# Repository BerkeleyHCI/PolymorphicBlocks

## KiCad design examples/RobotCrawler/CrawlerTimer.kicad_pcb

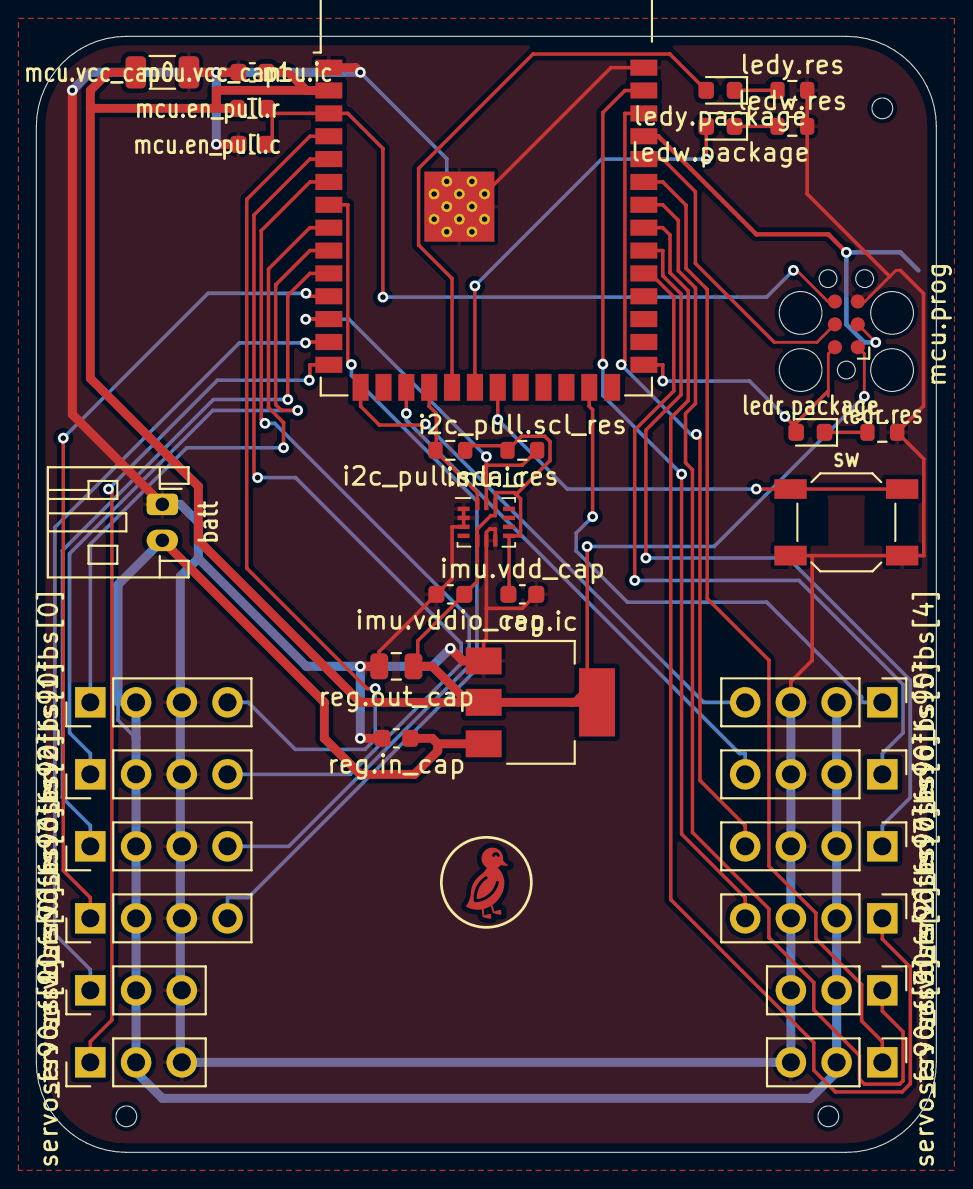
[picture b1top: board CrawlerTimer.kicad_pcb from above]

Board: 2 copper layers, 50.0 x 62.0 mm, 38 parts (0 on the bottom side), 35 nets.

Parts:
U4: Symbol_DucklingSolid
batt: S2B-PH-K; JST_PH_S2B-PH-K_1x02_P2.00mm_Horizontal
i2c_pull.scl_res, i2c_pull.sda_res: R_0603_1608Metric
imu.ic: LSM6DS3TR-C; Bosch_LGA-14_3x2.5mm_P0.5mm
imu.vdd_cap, imu.vddio_cap: C_0603_1608Metric
jlc_th.th1, jlc_th.th2, jlc_th.th3: JlcToolingHole_1.152mm
ledr.package: Red 615~630nm 1.9~2.2V 0603 Light Emitting Diodes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; LED_0603_1608Metric
ledr.res: R_0603_1608Metric
ledw.package: Red 615~630nm 1.9~2.2V 0603 Light Emitting Diodes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; LED_0603_1608Metric
ledw.res: R_0603_1608Metric
ledy.package: Red 615~630nm 1.9~2.2V 0603 Light Emitting Diodes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; LED_0603_1608Metric
ledy.res: R_0603_1608Metric
mcu.en_pull.c, mcu.vcc_cap1: C_0603_1608Metric
mcu.en_pull.r: R_0603_1608Metric
mcu.ic: ESP32-S3-WROOM-1-N16R8; ESP32-S3-WROOM-1
mcu.prog: Tag-Connect_TC2030-IDC-FP_2x03_P1.27mm_Vertical
mcu.vcc_cap0: C_1206_3216Metric
reg.ic: LDL1117S33R; SOT-223-3_TabPin2
reg.in_cap: C_0603_1608Metric
reg.out_cap: C_0805_2012Metric
servo_fs90fbs[0], servo_fs90fbs[1], servo_fs90fbs[2], servo_fs90fbs[3], servo_fs90fbs[4], servo_fs90fbs[5], servo_fs90fbs[6], servo_fs90fbs[7]: PinHeader2.54 1x4; PinHeader_1x04_P2.54mm_Vertical
servo_fs90rs[0], servo_fs90rs[1], servo_fs90rs[2], servo_fs90rs[3]: PinHeader2.54 1x3; PinHeader_1x03_P2.54mm_Vertical
sw: 5.1mm switch; SW_SPST_SKQG_WithoutStem

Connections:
batt.gnd: batt.1, imu.ic.1, imu.ic.2, imu.ic.3, imu.ic.6, imu.ic.7, imu.vdd_cap.2, imu.vddio_cap.2, ledr.res.2, ledw.res.2, ledy.res.2, mcu.en_pull.c.2, mcu.ic.1, mcu.ic.40, mcu.ic.41, mcu.prog.5, mcu.vcc_cap0.2, mcu.vcc_cap1.2, reg.ic.1, reg.in_cap.2, reg.out_cap.2, servo_fs90fbs[0].3, servo_fs90fbs[1].3, servo_fs90fbs[2].3, servo_fs90fbs[3].3, servo_fs90fbs[4].3, servo_fs90fbs[5].3, servo_fs90fbs[6].3, servo_fs90fbs[7].3, servo_fs90rs[0].3, servo_fs90rs[1].3, servo_fs90rs[2].3, servo_fs90rs[3].3, sw.2
batt.pwr: batt.2, reg.ic.3, reg.in_cap.1, servo_fs90fbs[0].2, servo_fs90fbs[1].2, servo_fs90fbs[2].2, servo_fs90fbs[3].2, servo_fs90fbs[4].2, servo_fs90fbs[5].2, servo_fs90fbs[6].2, servo_fs90fbs[7].2, servo_fs90rs[0].2, servo_fs90rs[1].2, servo_fs90rs[2].2, servo_fs90rs[3].2
i2c_pull.i2c.scl: i2c_pull.scl_res.2, imu.ic.13, mcu.ic.12
i2c_pull.i2c.sda: i2c_pull.sda_res.2, imu.ic.14, mcu.ic.18
imu.pwr: i2c_pull.scl_res.1, i2c_pull.sda_res.1, imu.ic.5, imu.ic.8, imu.ic.12, imu.vdd_cap.1, imu.vddio_cap.1, mcu.en_pull.r.1, mcu.ic.2, mcu.prog.1, mcu.vcc_cap0.1, mcu.vcc_cap1.1, reg.ic.2, reg.out_cap.1
ledr.res.a: ledr.package.1, ledr.res.1
ledw.res.a: ledw.package.1, ledw.res.1
ledw.signal: ledw.package.2, mcu.ic.20
ledy.res.a: ledy.package.1, ledy.res.1
ledy.signal: ledy.package.2, mcu.ic.19
mcu.program_boot_node: ledr.package.2, mcu.ic.27, mcu.prog.2
mcu.program_en_node: mcu.en_pull.c.1, mcu.en_pull.r.2, mcu.ic.3, mcu.prog.6
mcu.program_uart_node.a_tx: mcu.ic.37, mcu.prog.3
mcu.program_uart_node.b_tx: mcu.ic.36, mcu.prog.4
servo_fs90fbs[0].fb: mcu.ic.4, servo_fs90fbs[0].4
servo_fs90fbs[0].pwm: mcu.ic.8, servo_fs90fbs[0].1
servo_fs90fbs[1].fb: mcu.ic.5, servo_fs90fbs[1].4
servo_fs90fbs[1].pwm: mcu.ic.9, servo_fs90fbs[1].1
servo_fs90fbs[2].fb: mcu.ic.6, servo_fs90fbs[2].4
servo_fs90fbs[2].pwm: mcu.ic.10, servo_fs90fbs[2].1
servo_fs90fbs[3].fb: mcu.ic.7, servo_fs90fbs[3].4
servo_fs90fbs[3].pwm: mcu.ic.11, servo_fs90fbs[3].1
servo_fs90fbs[4].fb: mcu.ic.15, servo_fs90fbs[4].4
servo_fs90fbs[4].pwm: mcu.ic.25, servo_fs90fbs[4].1
servo_fs90fbs[5].fb: mcu.ic.17, servo_fs90fbs[5].4
servo_fs90fbs[5].pwm: mcu.ic.31, servo_fs90fbs[5].1
servo_fs90fbs[6].fb: mcu.ic.38, servo_fs90fbs[6].4
servo_fs90fbs[6].pwm: mcu.ic.32, servo_fs90fbs[6].1
servo_fs90fbs[7].fb: mcu.ic.39, servo_fs90fbs[7].4
servo_fs90fbs[7].pwm: mcu.ic.33, servo_fs90fbs[7].1
servo_fs90rs[0].pwm: mcu.ic.13, servo_fs90rs[0].1
servo_fs90rs[1].pwm: mcu.ic.14, servo_fs90rs[1].1
servo_fs90rs[2].pwm: mcu.ic.34, servo_fs90rs[2].1
servo_fs90rs[3].pwm: mcu.ic.35, servo_fs90rs[3].1
sw.out: mcu.ic.21, sw.1

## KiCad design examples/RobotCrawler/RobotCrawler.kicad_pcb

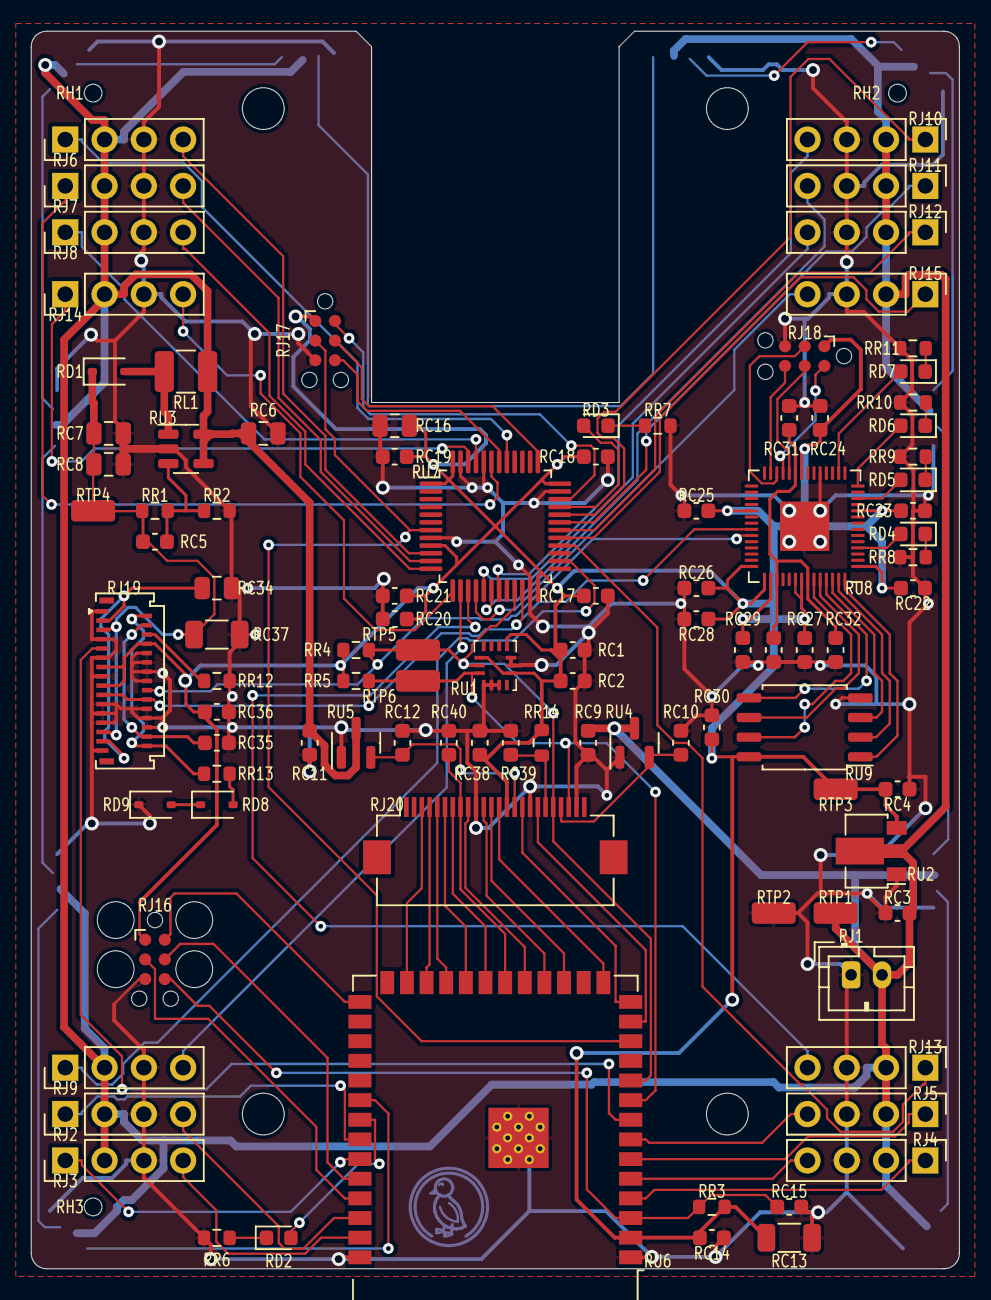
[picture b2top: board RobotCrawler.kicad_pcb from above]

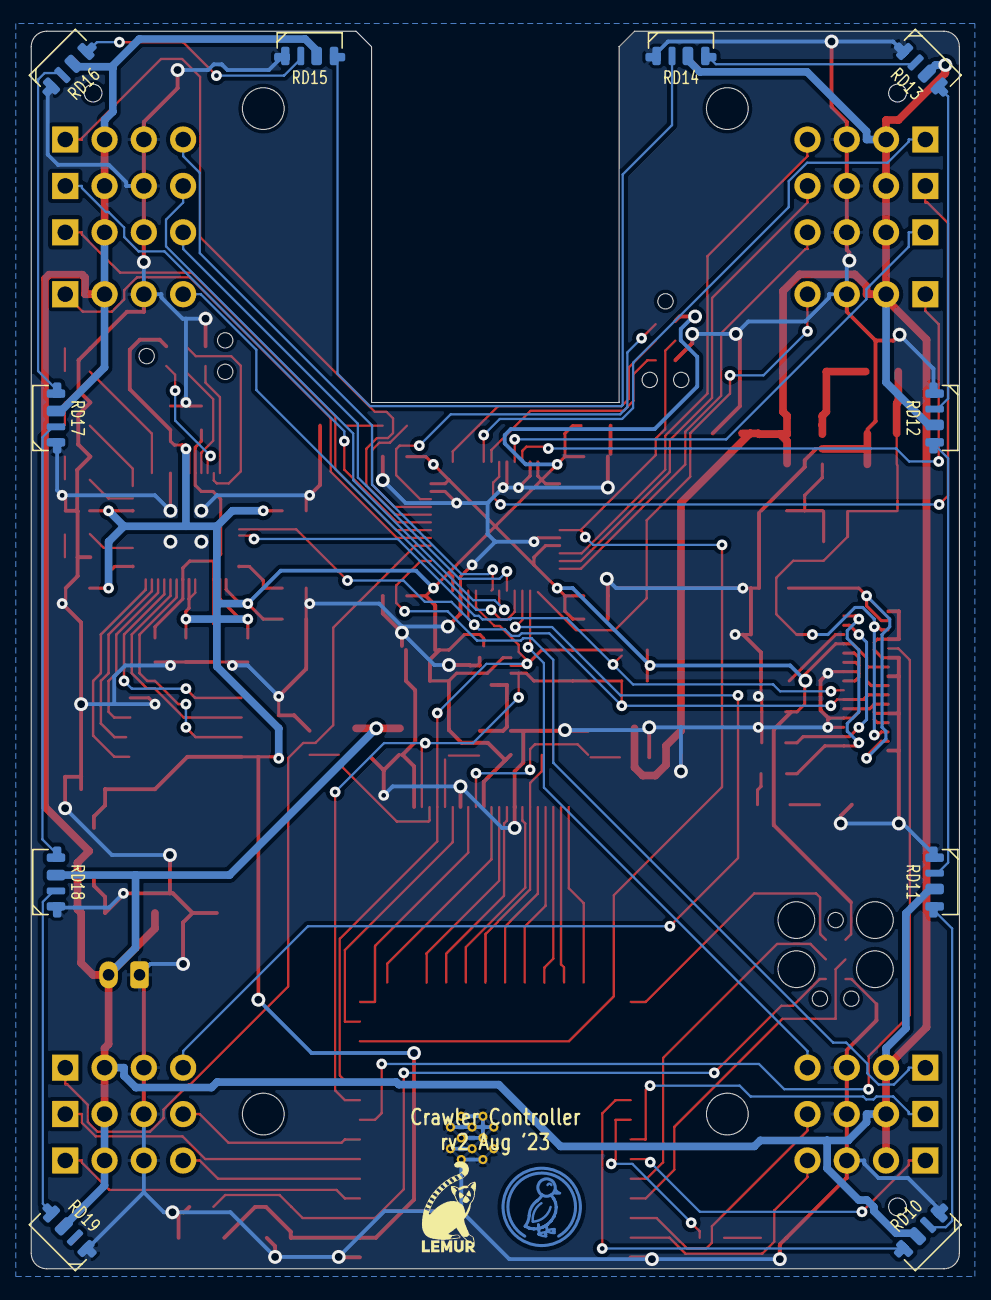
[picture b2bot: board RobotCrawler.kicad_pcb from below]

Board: 2 copper layers, 60.0 x 80.0 mm, 118 parts (12 on the bottom side), 99 nets.

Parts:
H10, H11, H12, H14: MountingHole_2.7mm_M2.5
RC1, RC2, RC3, RC4, RC5, RC9, RC10, RC11, RC12, RC14, RC15, RC17, RC18, RC19, RC20, RC21, RC22, RC23, RC24, RC25, RC26, RC27, RC28, RC29, RC30, RC31, RC32, RC33, RC35, RC36, RC38, RC39, RC40: C_0603_1608Metric
RC6, RC7, RC8, RC16, RC34: C_0805_2012Metric
RC13, RC37: C_1206_3216Metric
RD1: CUS10S30,H3F (TOSHIBA) - 30V 230mV@100mA 1A SOD-3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; D_SOD-323
RD2, RD3, RD4, RD5, RD6, RD7: LED_0603_1608Metric
RD8, RD9: 1N5819WS (Guangdong Hottech) - 40V 600mV@1A 1A SO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; D_SOD-323
RD10, RD11, RD12, RD13, RD14, RD15, RD16, RD17, RD18, RD19: SK6812 SIDE-A (Normand Electronic Co Ltd); LED_SK6812-SIDE-A
RH1, RH2, RH3: JlcToolingHole_1.152mm
RJ1: B2B-PH-K (JST); JST_PH_B2B-PH-K_1x02_P2.00mm_Vertical
RJ2, RJ3, RJ4, RJ5, RJ6, RJ7, RJ8, RJ9, RJ10, RJ11, RJ12, RJ13, RJ14, RJ15: PinHeader2.54 1x4 (Generic); PinHeader_1x04_P2.54mm_Vertical
RJ16: Tag-Connect_TC2030-IDC-FP_2x03_P1.27mm_Vertical
RJ17, RJ18: Tag-Connect_TC2030-IDC-NL_2x03_P1.27mm_Vertical
RJ19: FH35C-31S-0.3SHW (Hirose); Hirose_FH35C-31S-0.3SHW_1x31-1MP_P0.30mm_Horizontal
RJ20: AFC01-S24FCA-00 (Jushuo); Hirose_FH12-24S-0.5SH_1x24-1MP_P0.50mm_Horizontal
RL1: L_1210_3225Metric
RR1, RR2, RR3, RR4, RR5, RR6, RR7, RR8, RR9, RR10, RR11, RR12, RR13, RR14: R_0603_1608Metric
RTP1: 5015 (Keystone) - vbatt; TestPoint_TE_RCT_0805
RTP2: 5015 (Keystone) - gnd; TestPoint_TE_RCT_0805
RTP3: 5015 (Keystone) - v3v3; TestPoint_TE_RCT_0805
RTP4: 5015 (Keystone) - v14; TestPoint_TE_RCT_0805
RTP5: 5015 (Keystone) - i2c_chain_0.scl; TestPoint_TE_RCT_0805
RTP6: 5015 (Keystone) - i2c_tp._io_sda_link; TestPoint_TE_RCT_0805
RU1: LSM6DS3TR-C (STMicroelectronics); Bosch_LGA-14_3x2.5mm_P0.5mm
RU2: AP7215-33YG-13 (Diodes Incorporated); SOT-89-3
RU3: TPS61040DBVR (Texas Instruments); SOT-23-5
RU4: XC6206P252MR (Torex Semiconductor Ltd); SOT-23
RU5: XC6206P122MR-G (Torex Semiconductor Ltd); SOT-23
RU6: ESP32-S3-WROOM-1-N16R8 (Espressif Systems); ESP32-S3-WROOM-1
RU7: STM32F103xxT6 (STMicroelectronics); LQFP-48_7x7mm_P0.5mm
RU8: RP2040 (Raspberry Pi); QFN-56-1EP_7x7mm_P0.4mm_EP3.2x3.2mm
RU9: W25Q128JVSIQ (Winbond Electronics); SOIC-8_5.23x5.23mm_P1.27mm
UU4: Duck; Symbol_Duckling
UU5: Lemur; Symbol_LemurSmall

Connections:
Rcam.device.reset: RC39.1, RJ20.19, RR14.2
Rcam.dvp8.href: RJ20.16, RU6.14
Rcam.dvp8.pclk: RC40.1, RJ20.8, RU6.20
Rcam.dvp8.vsync: RJ20.18, RU6.13
Rcam.dvp8.xclk: RJ20.12, RU6.17
Rcam.dvp8.y0: RJ20.6, RU6.22
Rcam.dvp8.y1: RJ20.4, RU6.24
Rcam.dvp8.y2: RJ20.3, RU6.25
Rcam.dvp8.y3: RJ20.5, RU6.23
Rcam.dvp8.y4: RJ20.7, RU6.21
Rcam.dvp8.y5: RJ20.9, RU6.19
Rcam.dvp8.y6: RJ20.11, RU6.18
Rcam.dvp8.y7: RJ20.13, RU6.15
Rgnd: RC1.2, RC2.2, RC3.2, RC4.2, RC6.2, RC7.2, RC8.2, RC9.2, RC10.2, RC11.2, RC12.2, RC13.2, RC14.2, RC15.2, RC16.2, RC17.2, RC18.2, RC19.2, RC20.2, RC21.2, RC22.2, RC23.2, RC24.2, RC25.2, RC26.2, RC27.2, RC28.2, RC29.2, RC30.2, RC31.2, RC32.2, RC33.2, RC34.2, RC35.2, RC36.2, RC37.2, RC38.2, RC39.2, RC40.2, RD9.1, RD10.4, RD11.4, RD12.4, RD13.4, RD14.4, RD15.4, RD16.4, RD17.4, RD18.4, RD19.4, RJ1.1, RJ2.3, RJ3.3, RJ4.3, RJ5.3, RJ6.3, RJ7.3, RJ8.3, RJ9.3, RJ10.3, RJ11.3, RJ12.3, RJ13.3, RJ14.3, RJ15.3, RJ16.5, RJ17.5, RJ18.5, RJ19.1, RJ19.7, RJ19.10, RJ19.11, RJ19.12, RJ19.14, RJ19.15, RJ19.16, RJ19.21, RJ19.22, RJ19.23, RJ19.24, RJ19.25, RJ19.26, RJ19.31, RJ20.10, RJ20.17, RJ20.23, RR2.2, RR6.2, RR7.2, RR8.2, RR9.2, RR10.2, RR11.2, RR12.2, RTP2.1, RU1.1, RU1.2, RU1.3, RU1.6, RU1.7, RU2.1, RU3.2, RU4.1, RU5.1, RU6.1, RU6.40, RU6.41, RU7.8, RU7.23, RU7.35, RU7.44, RU7.47, RU8.19, RU8.57, RU9.4
Ri2c_chain_0.scl: RJ19.18, RJ20.20, RR4.2, RTP5.1, RU1.13, RU6.10, RU7.21, RU8.37
Ri2c_chain_0.sda: RJ19.19, RJ19.20, RJ20.22, RR5.2, RTP6.1, RU1.14, RU6.9, RU7.22, RU8.36
Rled.res.a: RD2.1, RR6.1
Rled.signal: RD2.2, RU6.33
Rmcu.program_boot_node: RJ16.2, RU6.27
Rmcu.program_en_node: RC15.1, RJ16.6, RR3.2, RU6.3
Rmcu.program_uart_node.a_tx: RJ16.3, RU6.37
Rmcu.program_uart_node.b_tx: RJ16.4, RU6.36
Rmcu_servo.reset_node: RJ17.3, RU6.12, RU7.7
Rmcu_servo.swd.swo: RJ17.6, RU7.42
Rmcu_servo.swd_node.swclk: RJ17.4, RU7.37
Rmcu_servo.swd_node.swdio: RJ17.2, RU7.34
Rmcu_test.gpio.led_0: RD4.2, RU8.4
Rmcu_test.gpio.led_1: RD5.2, RU8.12
Rmcu_test.gpio.led_2: RD6.2, RU8.14
Rmcu_test.gpio.led_3: RD7.2, RU8.16
Rmcu_test.ic.qspi.miso: RU8.55, RU9.2
Rmcu_test.ic.qspi.mosi: RU8.53, RU9.5
Rmcu_test.ic.qspi.sck: RU8.52, RU9.6
Rmcu_test.ic.qspi_cs: RU8.56, RU9.1
Rmcu_test.ic.qspi_sd2: RU8.54, RU9.3
Rmcu_test.ic.qspi_sd3: RU8.51, RU9.7
Rmcu_test.ic.vreg_vout: RC31.1, RC32.1, RC33.1, RU8.23, RU8.45, RU8.50
Rmcu_test.reset_node: RJ18.3, RU8.26
Rmcu_test.swd.swo: RJ18.6, RU8.27
Rmcu_test.swd_node.swclk: RJ18.4, RU8.24
Rmcu_test.swd_node.swdio: RJ18.2, RU8.25
Roled.device.vcomh: RC34.1, RJ19.3, RJ19.29
Roled.device.vp: RC35.1, RJ19.4, RJ19.28
Roled.device.vsl: RJ19.2, RJ19.30, RR13.1
Roled.iref_res.a: RJ19.6, RR12.1
Roled.reset: RJ19.9, RU6.8
Roled.vsl_d1.cathode: RD8.1, RD9.2
Roled.vsl_res.b: RD8.2, RR13.2
Rreg_14v.fb.output: RC5.2, RR1.2, RR2.1, RU3.3
Rreg_14v.inductor.b: RD1.2, RL1.2, RU3.1
Rrgbs.din: RD10.1, RU6.32
Rrgbs.led[0].dout: RD10.3, RD11.1
Rrgbs.led[1].dout: RD11.3, RD12.1
Rrgbs.led[2].dout: RD12.3, RD13.1
Rrgbs.led[3].dout: RD13.3, RD14.1
Rrgbs.led[4].dout: RD14.3, RD15.1
Rrgbs.led[5].dout: RD15.3, RD16.1
Rrgbs.led[6].dout: RD16.3, RD17.1
Rrgbs.led[7].dout: RD17.3, RD18.1
Rrgbs.led[8].dout: RD18.3, RD19.1
Rservo_led.res.a: RD3.1, RR7.1
Rservo_led.signal: RD3.2, RU7.33
Rservos[0].fb: RJ2.4, RU6.38
Rservos[0].pwm: RJ2.1, RU6.34
Rservos[1].fb: RJ3.4, RU6.39
Rservos[1].pwm: RJ3.1, RU6.35
Rservos[2].fb: RJ4.4, RU6.5
Rservos[2].pwm: RJ4.1, RU6.4
Rservos[3].fb: RJ5.4, RU6.7
Rservos[3].pwm: RJ5.1, RU6.6
Rservos[4].fb: RJ6.4, RU7.10
Rservos[4].pwm: RJ6.1, RU7.41
Rservos[5].fb: RJ7.4, RU7.11
Rservos[5].pwm: RJ7.1, RU7.43
Rservos[6].fb: RJ8.4, RU7.12
Rservos[6].pwm: RJ8.1, RU7.45
Rservos[7].fb: RJ9.4, RU7.14
Rservos[7].pwm: RJ9.1, RU7.26
Rservos[8].fb: RJ10.4, RU7.19
Rservos[8].pwm: RJ10.1, RU7.32
Rservos[9].fb: RJ11.4, RU7.18
Rservos[9].pwm: RJ11.1, RU7.31
Rservos[10].fb: RJ12.4, RU7.17
Rservos[10].pwm: RJ12.1, RU7.30
Rservos[11].fb: RJ13.4, RU7.15
Rservos[11].pwm: RJ13.1, RU7.28
Rservos_cam[0].fb: RJ14.4, RU7.13
Rservos_cam[0].pwm: RJ14.1, RU7.46
Rservos_cam[1].fb: RJ15.4, RU7.16
Rservos_cam[1].pwm: RJ15.1, RU7.29
Rtest_led.led[0].res.a: RD4.1, RR8.1
Rtest_led.led[1].res.a: RD5.1, RR9.1
Rtest_led.led[2].res.a: RD6.1, RR10.1
Rtest_led.led[3].res.a: RD7.1, RR11.1
Rv1v2: RC12.1, RJ20.15, RU5.2
Rv2v5: RC10.1, RJ20.21, RU4.2
Rv3v3: RC1.1, RC2.1, RC4.1, RC13.1, RC14.1, RC16.1, RC17.1, RC18.1, RC19.1, RC20.1, RC21.1, RC22.1, RC23.1, RC24.1, RC25.1, RC26.1, RC27.1, RC28.1, RC29.1, RC30.1, RC36.1, RC38.1, RJ16.1, RJ17.1, RJ18.1, RJ19.8, RJ19.13, RJ19.17, RJ20.14, RR3.1, RR4.1, RR5.1, RR14.1, RTP3.1, RU1.5, RU1.8, RU1.12, RU2.3, RU6.2, RU7.1, RU7.9, RU7.24, RU7.36, RU7.48, RU8.1, RU8.10, RU8.22, RU8.33, RU8.42, RU8.43, RU8.44, RU8.48, RU8.49, RU9.8
Rv14: RC5.1, RC7.1, RC8.1, RC37.1, RD1.1, RJ19.5, RJ19.27, RR1.1, RTP4.1
Rvbatt: RC3.1, RC6.1, RC9.1, RC11.1, RD10.2, RD11.2, RD12.2, RD13.2, RD14.2, RD15.2, RD16.2, RD17.2, RD18.2, RD19.2, RJ1.2, RJ2.2, RJ3.2, RJ4.2, RJ5.2, RJ6.2, RJ7.2, RJ8.2, RJ9.2, RJ10.2, RJ11.2, RJ12.2, RJ13.2, RJ14.2, RJ15.2, RL1.1, RTP1.1, RU2.2, RU3.4, RU3.5, RU4.3, RU5.3

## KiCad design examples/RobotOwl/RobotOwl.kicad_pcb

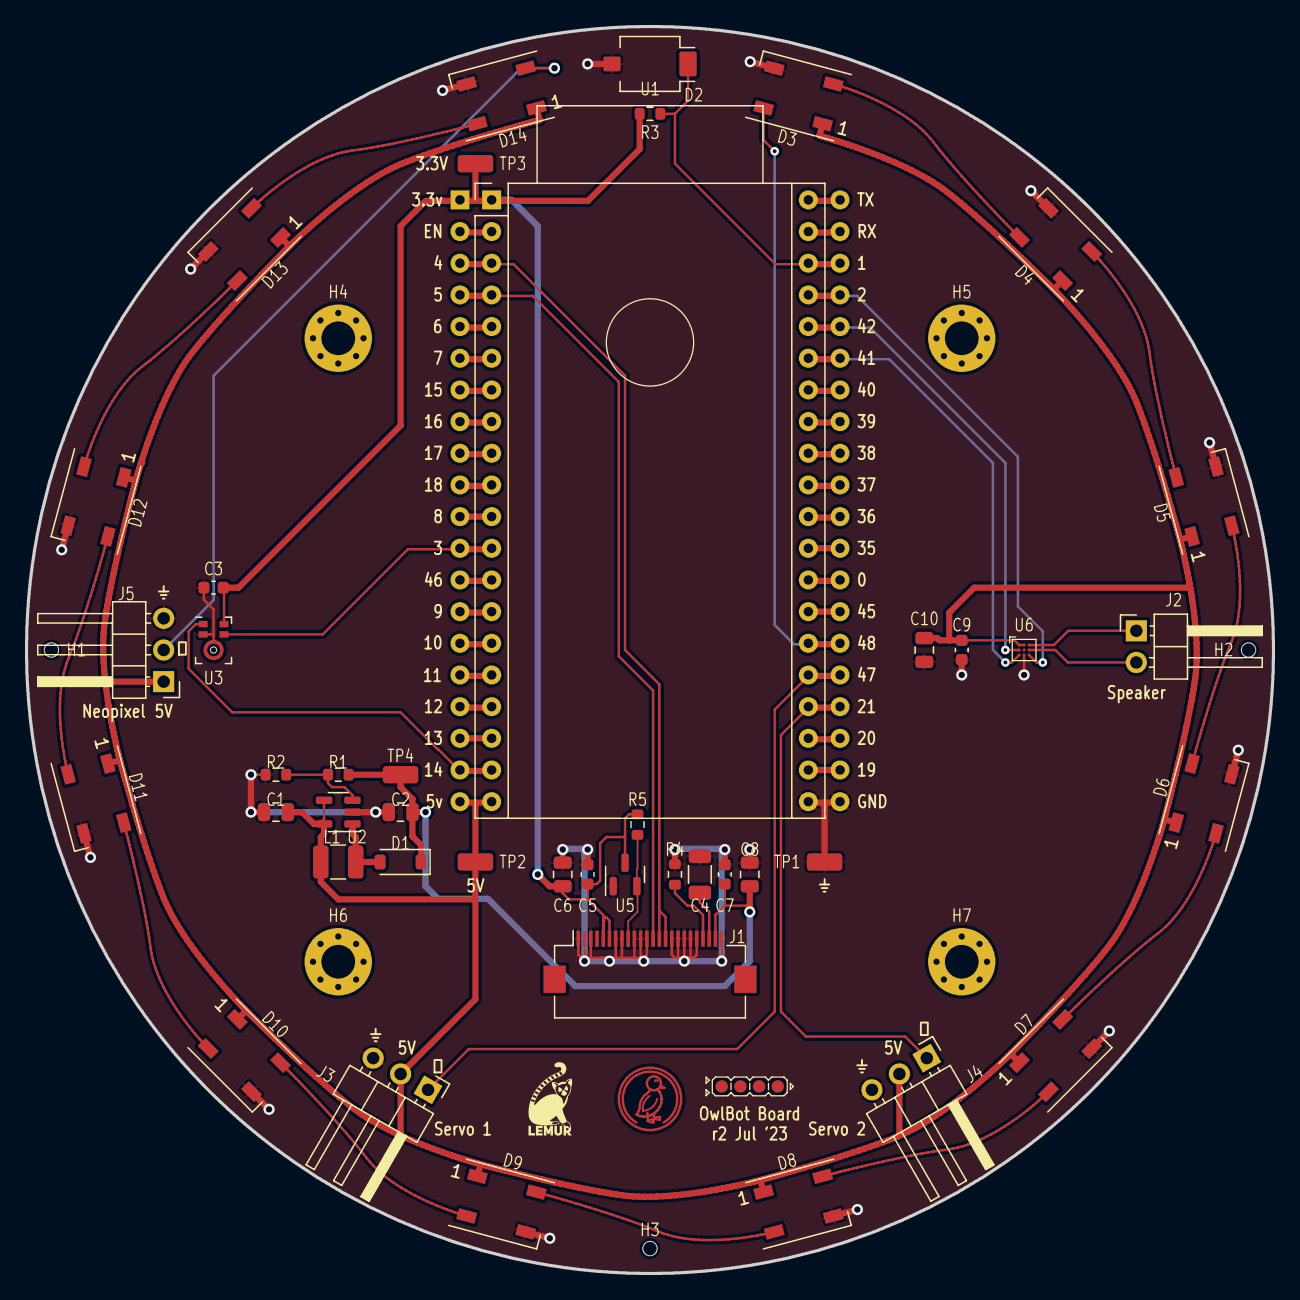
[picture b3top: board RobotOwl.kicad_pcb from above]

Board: 2 copper layers, 100.0 x 100.0 mm, 54 parts (0 on the bottom side), 34 nets.

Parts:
C1, C2, C6, C8, C10: C_0805_2012Metric
C3, C5, C7, C9: C_0603_1608Metric
C4: C_1206_3216Metric
D1: B0520W (Shikues) - 20V 390mV@500mA 500mA SOD-123 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; D_SOD-123
D2: Device:D_Photo - VBPW34S; Osram_BPW34S-SMD
D3, D4, D5, D6, D7, D8, D9, D10, D11, D12, D13, D14: WS2812B (Worldsemi); LED_WS2812B_PLCC4_5.0x5.0mm_P3.2mm
H1, H2, H3: JlcToolingHole_1.152mm
H4, H5, H6, H7: M2.5; MountingHole_2.7mm_M2.5_Pad_Via
J1: AFC01-S24FCA-00 (Jushuo); Hirose_FH12-24S-0.5SH_1x24-1MP_P0.50mm_Horizontal
J2: PinHeader2.54 1x2 Horizontal (Generic); PinHeader_1x02_P2.54mm_Horizontal
J3, J4, J5: PinHeader2.54 1x3 Horizontal (Generic); PinHeader_1x03_P2.54mm_Horizontal
L1: L_1210_3225Metric
R1, R2, R3, R4, R5: R_0603_1608Metric
TP1: 5015 (Keystone) - gnd; TestPoint_TE_RCT_0805
TP2: 5015 (Keystone) - vusb; TestPoint_TE_RCT_0805
TP3: 5015 (Keystone) - v3v3; TestPoint_TE_RCT_0805
TP4: 5015 (Keystone) - v12; TestPoint_TE_RCT_0805
U1: Freenove ESP32S3-WROOM; Freenove_ESP32S3-WROOM_Expansion
U2: AP3012K (Diodes Incorporated); SOT-23-5
U3: SD18OB261-060 (Goertek); Knowles_LGA-5_3.5x2.65mm
U5: APX803S-29SA-7 (Diodes Incorporated); SOT-23
U6: MAX98357AEWL+T (Maxim Integrated); Maxim_WLP-9_1.595x1.415_Layout3x3_P0.4mm_Ball0.27mm_Pad0.25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
UU4: Duck; Symbol_Duckling
UU5: Lemur; Symbol_LemurSmall
UU6: IdDots4; Indicator_IdDots_4

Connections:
gnd: C1.2, C2.2, C3.2, C4.2, C5.2, C6.2, C7.2, C8.2, C9.2, C10.2, D2.2, D3.3, D4.3, D5.3, D6.3, D7.3, D8.3, D9.3, D10.3, D11.3, D12.3, D13.3, D14.3, J1.1, J1.2, J1.3, J1.7, J1.8, J1.10, J1.11, J1.12, J1.16, J1.17, J1.18, J1.19, J1.20, J1.24, J3.3, J4.3, J5.3, R2.2, R4.2, TP1.1, U1.21, U2.2, U3.2, U3.3, U5.1, U6.C2
mic.clk: U1.12, U3.4
mic.data: U1.19, U3.1
oled22.device.vcomh: C4.1, J1.22
oled22.i2c.scl: J1.13, U1.4
oled22.i2c.sda: J1.14, J1.15, U1.3
oled22.iref_res.a: J1.21, R4.1
oled_rst.nreset: J1.9, R5.2, U5.2
photodiode.out: D2.1, R3.2, U1.38
reg_12v.fb.output: R1.2, R2.1, U2.3
reg_12v.power_path.switch: D1.2, L1.2, U2.1
servo[0].pwm: J3.1, U1.25
servo[1].pwm: J4.1, U1.24
spk_drv.i2s.sck: U1.35, U6.C1
spk_drv.i2s.sd: U1.36, U6.B1
spk_drv.i2s.ws: U1.37, U6.C3
spk_drv.out.a: J2.1, U6.A3
spk_drv.out.b: J2.2, U6.B3
v3v3: C3.1, C5.1, C6.1, J1.5, J1.6, R3.1, R5.1, TP3.1, U1.1, U3.5, U5.3
v12: C2.1, C7.1, C8.1, D1.1, J1.23, R1.1, TP4.1
vusb: C1.1, C9.1, C10.1, D3.1, D4.1, D5.1, D6.1, D7.1, D8.1, D9.1, D10.1, D11.1, D12.1, D13.1, D14.1, J3.2, J4.2, J5.1, L1.1, TP2.1, U1.20, U2.4, U2.5, U6.A1, U6.A2
ws2812bArray.din: D3.4, U1.26
ws2812bArray.dout: D14.2, J5.2
ws2812bArray.led[0].dout: D3.2, D4.4
ws2812bArray.led[1].dout: D4.2, D5.4
ws2812bArray.led[2].dout: D5.2, D6.4
ws2812bArray.led[3].dout: D6.2, D7.4
ws2812bArray.led[4].dout: D7.2, D8.4
ws2812bArray.led[5].dout: D8.2, D9.4
ws2812bArray.led[6].dout: D9.2, D10.4
ws2812bArray.led[7].dout: D10.2, D11.4
ws2812bArray.led[8].dout: D11.2, D12.4
ws2812bArray.led[9].dout: D12.2, D13.4
ws2812bArray.led[10].dout: D13.2, D14.4

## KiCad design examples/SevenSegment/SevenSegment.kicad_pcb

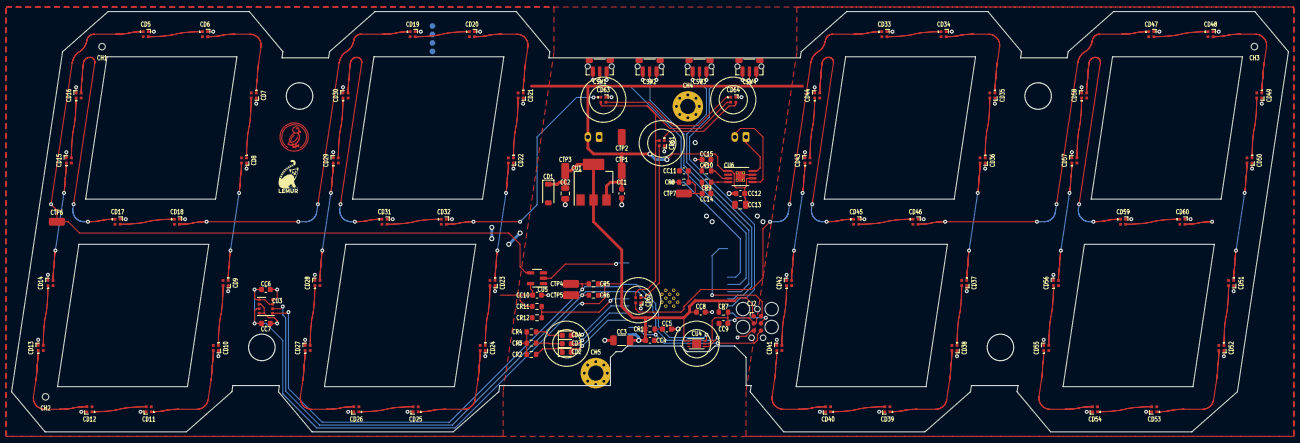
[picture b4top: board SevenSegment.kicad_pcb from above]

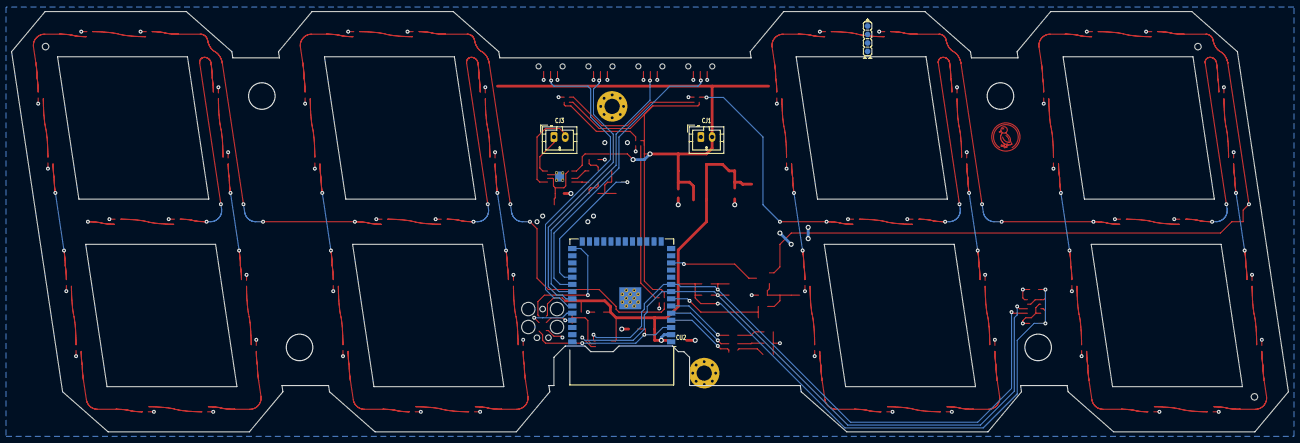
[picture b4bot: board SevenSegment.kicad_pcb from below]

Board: 2 copper layers, 226.0 x 74.4 mm, 119 parts (4 on the bottom side), 90 nets.

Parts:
CC1, CC4, CC5, CC6, CC7, CC8, CC9, CC10, CC11, CC12, CC14, CC15: C_0603_1608Metric
CC2, CC13: C_0805_2012Metric
CC3: C_1206_3216Metric
CD1: BZT52C3V6 (SMC(Sangdest Microelectronicstronic (N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; D_SOD-123
CD2: KT-0603R (Hubei KENTO Elec) - Red 615~630nm 1.9~2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; LED_0603_1608Metric
CD3, CD4: LED_0603_1608Metric
CD5, CD6, CD7, CD8, CD9, CD10, CD11, CD12, CD13, CD14, CD15, CD16, CD17, CD18, CD19, CD20, CD21, CD22, CD23, CD24, CD25, CD26, CD27, CD28, CD29, CD30, CD31, CD32, CD33, CD34, CD35, CD36, CD37, CD38, CD39, CD40, CD41, CD42, CD43, CD44, CD45, CD46, CD47, CD48, CD49, CD50, CD51, CD52, CD53, CD54, CD55, CD56, CD57, CD58, CD59, CD60, CD61, CD62, CD63, CD64: SK6805-EC15 (Opsco Optoelectronics); LED_SK6812_EC15_1.5x1.5mm
CH1, CH2, CH3: JlcToolingHole_1.152mm
CH4, CH5: M2.5; MountingHole_2.7mm_M2.5_Pad_Via
CJ1, CJ3: B2B-PH-K (JST); JST_PH_B2B-PH-K_1x02_P2.00mm_Vertical
CJ2: Tag-Connect_TC2030-IDC-FP_2x03_P1.27mm_Vertical
CR1, CR2, CR3, CR4, CR5, CR6, CR7, CR8, CR9, CR10, CR11, CR12: R_0603_1608Metric
CSW1, CSW2, CSW3, CSW4: SKRTLAE010 (Alps Alpine); SW_Push_1P1T-MP_NO_Horizontal_Alps_SKRTLAE010
CTP1: 5015 (Keystone) - pwr; TestPoint_TE_RCT_0805
CTP2: 5015 (Keystone) - gnd; TestPoint_TE_RCT_0805
CTP3: 5015 (Keystone) - v3v3; TestPoint_TE_RCT_0805
CTP4: 5015 (Keystone) - i2c_chain_0.scl; TestPoint_TE_RCT_0805
CTP5: 5015 (Keystone) - i2c_tp._io_sda_link; TestPoint_TE_RCT_0805
CTP6: 5015 (Keystone) - _rgb_shift_output_link; TestPoint_TE_RCT_0805
CTP7: 5015 (Keystone) - spk_chain_1; TestPoint_TE_RCT_0805
CU1: LDL1117S33R (STMicroelectronics); SOT-223-3_TabPin2
CU2: ESP32-S3-WROOM-1-N16R8 (Espressif Systems); ESP32-S3-WROOM-1
CU3: BME680 (Bosch Sensortec); Bosch_LGA-8_3x3mm_P0.8mm_ClockwisePinNumbering
CU4: BH1750 (Rohm Semiconductor); HVSOF6
CU5: 74AHCT1G125W5-7 (Diodes Incorporated); SOT-23-5
CU6: TPA2005D1 (Texas Instruments); MSOP-8-1EP_3x3mm_P0.65mm_EP1.68x1.88mm_ThermalVias
UU4: Duck; Symbol_Duckling
UU5: Lemur; Symbol_LemurSmall
UU6: IdDots4; Indicator_IdDots_4

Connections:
als.dvi_res.b: CC9.1, CR7.2, CU4.5
center.dout: CD33.1, CD62.3
center.led[0].dout: CD61.3, CD62.1
digit[0].dout: CD18.3, CD19.1
digit[0].led[0].dout: CD5.3, CD6.1
digit[0].led[1].dout: CD6.3, CD7.1
digit[0].led[2].dout: CD7.3, CD8.1
digit[0].led[3].dout: CD8.3, CD9.1
digit[0].led[4].dout: CD9.3, CD10.1
digit[0].led[5].dout: CD10.3, CD11.1
digit[0].led[6].dout: CD11.3, CD12.1
digit[0].led[7].dout: CD12.3, CD13.1
digit[0].led[8].dout: CD13.3, CD14.1
digit[0].led[9].dout: CD14.3, CD15.1
digit[0].led[10].dout: CD15.3, CD16.1
digit[0].led[11].dout: CD16.3, CD17.1
digit[0].led[12].dout: CD17.3, CD18.1
digit[1].dout: CD32.3, CD63.1
digit[1].led[0].dout: CD19.3, CD20.1
digit[1].led[1].dout: CD20.3, CD21.1
digit[1].led[2].dout: CD21.3, CD22.1
digit[1].led[3].dout: CD22.3, CD23.1
digit[1].led[4].dout: CD23.3, CD24.1
digit[1].led[5].dout: CD24.3, CD25.1
digit[1].led[6].dout: CD25.3, CD26.1
digit[1].led[7].dout: CD26.3, CD27.1
digit[1].led[8].dout: CD27.3, CD28.1
digit[1].led[9].dout: CD28.3, CD29.1
digit[1].led[10].dout: CD29.3, CD30.1
digit[1].led[11].dout: CD30.3, CD31.1
digit[1].led[12].dout: CD31.3, CD32.1
digit[2].dout: CD46.3, CD47.1
digit[2].led[0].dout: CD33.3, CD34.1
digit[2].led[1].dout: CD34.3, CD35.1
digit[2].led[2].dout: CD35.3, CD36.1
digit[2].led[3].dout: CD36.3, CD37.1
digit[2].led[4].dout: CD37.3, CD38.1
digit[2].led[5].dout: CD38.3, CD39.1
digit[2].led[6].dout: CD39.3, CD40.1
digit[2].led[7].dout: CD40.3, CD41.1
digit[2].led[8].dout: CD41.3, CD42.1
digit[2].led[9].dout: CD42.3, CD43.1
digit[2].led[10].dout: CD43.3, CD44.1
digit[2].led[11].dout: CD44.3, CD45.1
digit[2].led[12].dout: CD45.3, CD46.1
digit[3].led[0].dout: CD47.3, CD48.1
digit[3].led[1].dout: CD48.3, CD49.1
digit[3].led[2].dout: CD49.3, CD50.1
digit[3].led[3].dout: CD50.3, CD51.1
digit[3].led[4].dout: CD51.3, CD52.1
digit[3].led[5].dout: CD52.3, CD53.1
digit[3].led[6].dout: CD53.3, CD54.1
digit[3].led[7].dout: CD54.3, CD55.1
digit[3].led[8].dout: CD55.3, CD56.1
digit[3].led[9].dout: CD56.3, CD57.1
digit[3].led[10].dout: CD57.3, CD58.1
digit[3].led[11].dout: CD58.3, CD59.1
digit[3].led[12].dout: CD59.3, CD60.1
gnd: CC1.2, CC2.2, CC3.2, CC4.2, CC5.2, CC6.2, CC7.2, CC8.2, CC9.2, CC10.2, CC11.2, CC12.2, CC13.2, CC15.2, CD1.2, CD5.4, CD6.4, CD7.4, CD8.4, CD9.4, CD10.4, CD11.4, CD12.4, CD13.4, CD14.4, CD15.4, CD16.4, CD17.4, CD18.4, CD19.4, CD20.4, CD21.4, CD22.4, CD23.4, CD24.4, CD25.4, CD26.4, CD27.4, CD28.4, CD29.4, CD30.4, CD31.4, CD32.4, CD33.4, CD34.4, CD35.4, CD36.4, CD37.4, CD38.4, CD39.4, CD40.4, CD41.4, CD42.4, CD43.4, CD44.4, CD45.4, CD46.4, CD47.4, CD48.4, CD49.4, CD50.4, CD51.4, CD52.4, CD53.4, CD54.4, CD55.4, CD56.4, CD57.4, CD58.4, CD59.4, CD60.4, CD61.4, CD62.4, CD63.4, CD64.4, CJ1.1, CJ2.5, CR2.2, CR3.2, CR4.2, CR12.2, CSW1.1, CSW2.1, CSW3.1, CSW4.1, CTP2.1, CU1.1, CU2.1, CU2.40, CU2.41, CU3.1, CU3.5, CU3.7, CU4.2, CU4.3, CU5.1, CU5.3, CU6.7, CU6.9
i2c_chain_0.scl: CR5.2, CTP4.1, CU2.9, CU3.4, CU4.6
i2c_chain_0.sda: CR6.2, CTP5.1, CU2.8, CU3.3, CU4.4
ledb.res.a: CD4.1, CR4.1
ledb.signal: CD4.2, CU2.6
ledg.res.a: CD3.1, CR3.1
ledg.signal: CD3.2, CU2.5
ledr.res.a: CD2.1, CR2.1
ledr.signal: CD2.2, CU2.4
mcu.program_boot_node: CJ2.2, CU2.27
mcu.program_en_node: CC5.1, CJ2.6, CR1.2, CU2.3
mcu.program_uart_node.a_tx: CJ2.3, CU2.37
mcu.program_uart_node.b_tx: CJ2.4, CU2.36
meta.dout: CD61.1, CD64.3
meta.led[0].dout: CD63.3, CD64.1
pwr: CC1.1, CC10.1, CC12.1, CC13.1, CD5.2, CD6.2, CD7.2, CD8.2, CD9.2, CD10.2, CD11.2, CD12.2, CD13.2, CD14.2, CD15.2, CD16.2, CD17.2, CD18.2, CD19.2, CD20.2, CD21.2, CD22.2, CD23.2, CD24.2, CD25.2, CD26.2, CD27.2, CD28.2, CD29.2, CD30.2, CD31.2, CD32.2, CD33.2, CD34.2, CD35.2, CD36.2, CD37.2, CD38.2, CD39.2, CD40.2, CD41.2, CD42.2, CD43.2, CD44.2, CD45.2, CD46.2, CD47.2, CD48.2, CD49.2, CD50.2, CD51.2, CD52.2, CD53.2, CD54.2, CD55.2, CD56.2, CD57.2, CD58.2, CD59.2, CD60.2, CD61.2, CD62.2, CD63.2, CD64.2, CJ1.2, CR11.1, CTP1.1, CU1.3, CU5.5, CU6.1, CU6.6
rgb_shift.input: CU2.12, CU5.2
rgb_shift.output: CD5.1, CTP6.1, CU5.4
spk_chain_0: CR8.1, CU2.31
spk_chain_1: CC11.1, CC14.2, CR8.2, CTP7.1
spk_chain_2.a: CJ3.1, CU6.8
spk_chain_2.b: CJ3.2, CU6.5
spk_drv.inn_cap.pos: CC15.1, CR10.1
spk_drv.inn_res.b: CR10.2, CU6.3
spk_drv.inp_cap.pos: CC14.1, CR9.1
spk_drv.inp_res.b: CR9.2, CU6.4
sw[0].out: CSW1.2, CU2.32
sw[1].out: CSW2.2, CU2.33
sw[2].out: CSW3.2, CU2.34
sw[3].out: CSW4.2, CU2.35
v3v3: CC2.1, CC3.1, CC4.1, CC6.1, CC7.1, CC8.1, CD1.1, CJ2.1, CR1.1, CR5.1, CR6.1, CR7.1, CTP3.1, CU1.2, CU2.2, CU3.2, CU3.6, CU3.8, CU4.1
v5v_sense.output: CR11.2, CR12.1, CU2.7

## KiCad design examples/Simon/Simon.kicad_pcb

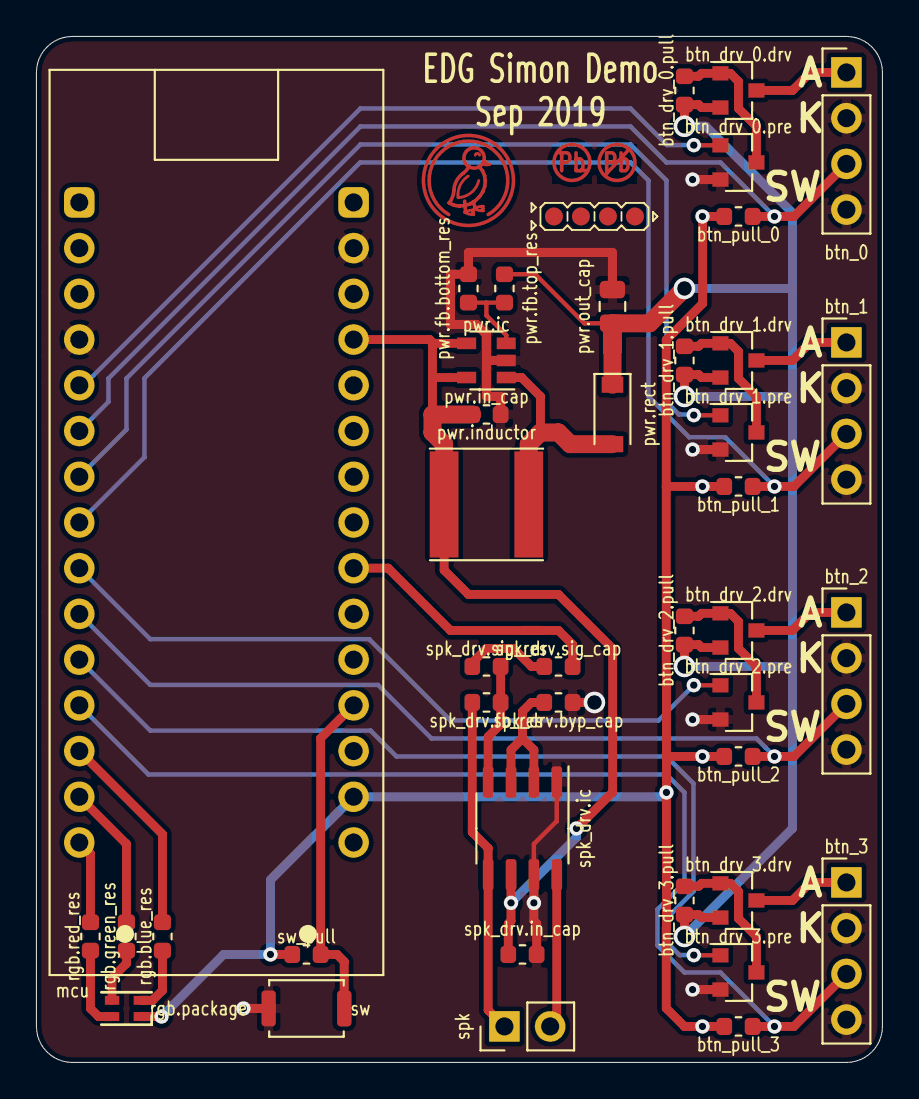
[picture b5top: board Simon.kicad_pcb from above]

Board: 2 copper layers, 47.0 x 57.0 mm, 44 parts (0 on the bottom side), 35 nets.

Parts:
btn_0, btn_1, btn_2, btn_3: DomeButton; PinHeader_1x04_P2.54mm_Vertical
btn_drv_0.drv, btn_drv_1.drv, btn_drv_2.drv, btn_drv_3.drv: DMP3099L-7; SOT-23
btn_drv_0.pre, btn_drv_1.pre, btn_drv_2.pre, btn_drv_3.pre: NX138AKR; SOT-23
btn_drv_0.pull, btn_drv_1.pull, btn_drv_2.pull, btn_drv_3.pull: 10000, 1%, 0.1W; R_0603_1608Metric
btn_pull_0, btn_pull_1, btn_pull_2, btn_pull_3: 10000, 1%, 0.1W; R_0603_1608Metric
duck: Duck; Symbol_Duckling
id: IdDots4; Indicator_IdDots_4
leadfree: LeadFree; Indicator_LeadFree
mcu: Nucleo-F303K8; Nucleo32
pwr.fb.bottom_res: 3900, 1%, 0.1W; R_0603_1608Metric
pwr.fb.top_res: 33000, 1%, 0.1W; R_0603_1608Metric
pwr.ic: AP3012; SOT-23-5
pwr.in_cap: 1µF, 10V, CL10A105KP8NNNC; C_0603_1608Metric
pwr.inductor: 68µH, 770mA, NR6028T680M; L_Taiyo-Yuden_NR-60xx
pwr.out_cap: 10µF, 16V, CL21A106KOQNNNG; C_0805_2012Metric
pwr.rect: BAT54GWJ; D_SOD-123
rgb.blue_res, rgb.green_res, rgb.red_res: 1000, 1%, 0.1W; R_0603_1608Metric
rgb.package: LED_RGB_0606
spk: Speaker SP-1504; PinHeader_1x02_P2.54mm_Vertical
spk_drv.byp_cap, spk_drv.in_cap: 1µF, 10V, CL10A105KP8NNNC; C_0603_1608Metric
spk_drv.fb_res, spk_drv.sig_res: 22000, 1%, 0.1W; R_0603_1608Metric
spk_drv.ic: LM4871MX; SO-8_3.9x4.9mm_P1.27mm
spk_drv.sig_cap: 0.47µF, 25V, CL10B474KA8NFNC; C_0603_1608Metric
sw: switch; SW_Push_SPST_NO_Alps_SKRK
sw_pull: 10000, 1%, 0.1W; R_0603_1608Metric

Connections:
btn_1.led_a: btn_1.1, btn_drv_1.drv.3
btn_2.sw1: btn_2.3, btn_pull_2.2, mcu.10
btn_drv_0.control: btn_drv_0.pre.1, mcu.5
btn_drv_0.output: btn_0.1, btn_drv_0.drv.3
btn_drv_0.pre.drain: btn_drv_0.drv.1, btn_drv_0.pre.3, btn_drv_0.pull.2
btn_drv_1.pull.b: btn_drv_1.drv.1, btn_drv_1.pre.3, btn_drv_1.pull.2
btn_drv_2.output: btn_2.1, btn_drv_2.drv.3
btn_drv_2.pre.drain: btn_drv_2.drv.1, btn_drv_2.pre.3, btn_drv_2.pull.2
btn_drv_3.control: btn_drv_3.pre.1, mcu.11
btn_drv_3.drv.gate: btn_drv_3.drv.1, btn_drv_3.pre.3, btn_drv_3.pull.2
btn_drv_3.output: btn_3.1, btn_drv_3.drv.3
gnd: btn_0.2, btn_0.4, btn_1.2, btn_1.4, btn_2.2, btn_2.4, btn_3.2, btn_3.4, btn_drv_0.pre.2, btn_drv_1.pre.2, btn_drv_2.pre.2, btn_drv_3.pre.2, mcu.4, mcu.17, pwr.fb.bottom_res.2, pwr.ic.2, pwr.in_cap.2, pwr.out_cap.2, spk_drv.byp_cap.2, spk_drv.ic.1, spk_drv.ic.7, spk_drv.in_cap.2, sw.1
mcu.dac_1: mcu.24, spk_drv.sig_cap.2
mcu.digital_9: btn_3.3, btn_pull_3.2, mcu.12
mcu.digital_12: btn_drv_2.pre.1, mcu.9
mcu.digital_13: btn_1.3, btn_pull_1.2, mcu.8
mcu.digital_14: btn_drv_1.pre.1, mcu.7
mcu.digital_15: btn_0.3, btn_pull_0.2, mcu.6
mcu.digital_17: mcu.27, sw.2, sw_pull.2
mcu.digital_18: mcu.13, rgb.blue_res.2
mcu.digital_19: mcu.14, rgb.green_res.2
pwr.fb.out: pwr.fb.bottom_res.1, pwr.fb.top_res.2, pwr.ic.3
pwr.sw: pwr.ic.1, pwr.inductor.2, pwr.rect.2
rgb.blue_res.a: rgb.blue_res.1, rgb.package.2
rgb.green_res.a: rgb.green_res.1, rgb.package.3
rgb.red: mcu.15, rgb.red_res.2
rgb.red_res.a: rgb.package.4, rgb.red_res.1
spk_drv.byp_cap.pos: spk_drv.byp_cap.1, spk_drv.ic.2, spk_drv.ic.3
spk_drv.sig_res.a: spk_drv.sig_cap.1, spk_drv.sig_res.1
spk_drv.sig_res.b: spk_drv.fb_res.1, spk_drv.ic.4, spk_drv.sig_res.2
spk_drv.spk1: spk.1, spk_drv.fb_res.2, spk_drv.ic.5
spk_drv.spk2: spk.2, spk_drv.ic.8
v3v3: btn_pull_0.1, btn_pull_1.1, btn_pull_2.1, btn_pull_3.1, mcu.29, rgb.package.1, sw_pull.1
v5: mcu.19, pwr.ic.4, pwr.ic.5, pwr.in_cap.1, pwr.inductor.1, spk_drv.ic.6, spk_drv.in_cap.1
v12: btn_drv_0.drv.2, btn_drv_0.pull.1, btn_drv_1.drv.2, btn_drv_1.pull.1, btn_drv_2.drv.2, btn_drv_2.pull.1, btn_drv_3.drv.2, btn_drv_3.pull.1, pwr.fb.top_res.1, pwr.out_cap.1, pwr.rect.1
